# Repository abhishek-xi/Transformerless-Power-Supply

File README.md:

# Transformerless Power Supply PCB Project

This repository contains the KiCad project files for a **Transformerless Power Supply**.

## Description
KiCad-based PCB design for a transformerless power supply circuit. The design provides AC to DC conversion using passive and active components without a bulky transformer, making it compact and cost-effective for low-power embedded or household electronics applications. Includes schematic, PCB layout, and Gerber files for fabrication.

## Contents
- `*.kicad_sch` – Main schematic
- `*.kicad_pcb` – PCB layout
- `*.kicad_pro` – Project configuration
- `*.drl` – Drill file
- `Gerber files` – Gerber outputs for fabrication

## How to Open
1. Install [KiCad](https://www.kicad.org/) (version 6 or newer recommended).
2. Clone this repository.
3. Open the project using the `.kicad_pro` file.

## Safety Note ⚠️
Transformerless power supplies operate directly from AC mains. They **do not provide galvanic isolation** and can be extremely dangerous if mishandled. These designs are recommended only for experienced users and low-power applications. Use caution and follow all electrical safety practices.

## License
[MIT License](LICENSE) – You are free to use, modify, and distribute this project.

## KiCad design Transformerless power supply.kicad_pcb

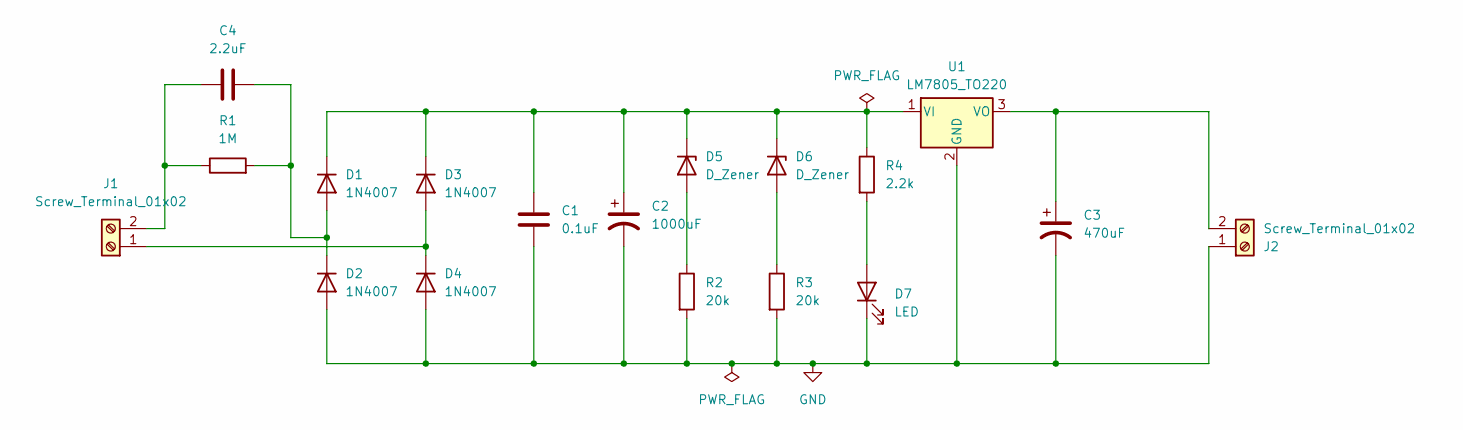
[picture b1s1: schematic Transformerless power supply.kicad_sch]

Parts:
C1: 0.1uF; C_Disc_D7.0mm_W2.5mm_P5.00mm
C2: 1000uF; CP_Radial_D10.0mm_P5.00mm
C3: 470uF; CP_Radial_D10.0mm_P3.80mm
C4: 2.2uF; C_Rect_L18.0mm_W6.0mm_P15.00mm_FKS3_FKP3
D1, D2, D3, D4: 1N4007; D_DO-41_SOD81_P10.16mm_Horizontal
D5, D6: D_Zener; D_A-405_P7.62mm_Horizontal
D7: LED; LED_D5.0mm
J1, J2: Screw_Terminal_01x02; TerminalBlock_bornier-2_P5.08mm
R1: 1M; R_Axial_DIN0207_L6.3mm_D2.5mm_P7.62mm_Horizontal
R2, R3: 20k; R_Axial_DIN0207_L6.3mm_D2.5mm_P7.62mm_Horizontal
R4: 2.2k; R_Axial_DIN0207_L6.3mm_D2.5mm_P7.62mm_Horizontal
U1: LM7805_TO220; TO-220-3_Vertical

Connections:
GND: C1.2, C2.2, C3.2, D2.2 (A), D4.2 (A), D7.1 (K), J2.1, R2.2, R3.2, U1.2 (GND)
unnamed: C4.2, D1.2 (A), D2.1 (K), R1.2
unnamed: C1.1, C2.1, D1.1 (K), D3.1 (K), D5.1 (K), D6.1 (K), R4.1, U1.1 (VI)
unnamed: D3.2 (A), D4.1 (K), J1.1
unnamed: D5.2 (A), R2.1
unnamed: D6.2 (A), R3.1
unnamed: D7.2 (A), R4.2
unnamed: C4.1, J1.2, R1.1
unnamed: C3.1, J2.2, U1.3 (VO)

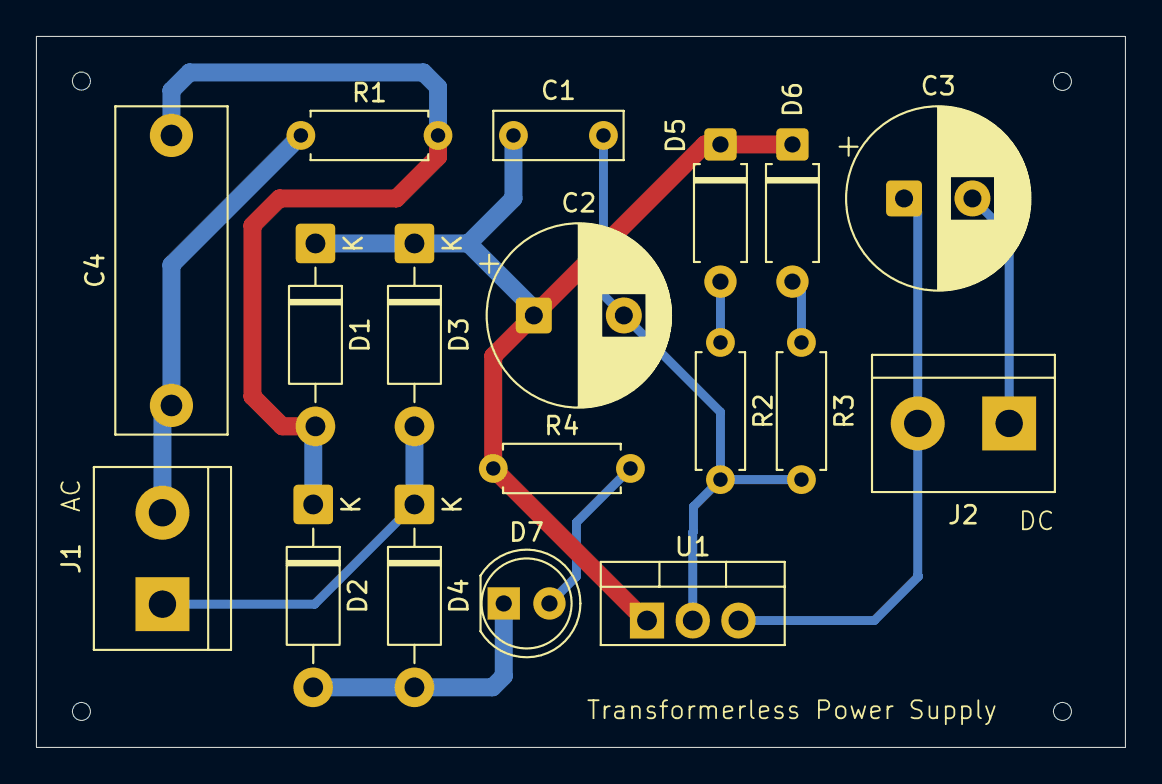
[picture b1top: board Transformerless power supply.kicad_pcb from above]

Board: 2 copper layers, 60.5 x 39.5 mm, 18 parts (0 on the bottom side), 9 nets.
